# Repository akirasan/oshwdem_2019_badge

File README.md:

# oshwdem_2019_badge
Badge Oshwi para la OSHWDem 2019

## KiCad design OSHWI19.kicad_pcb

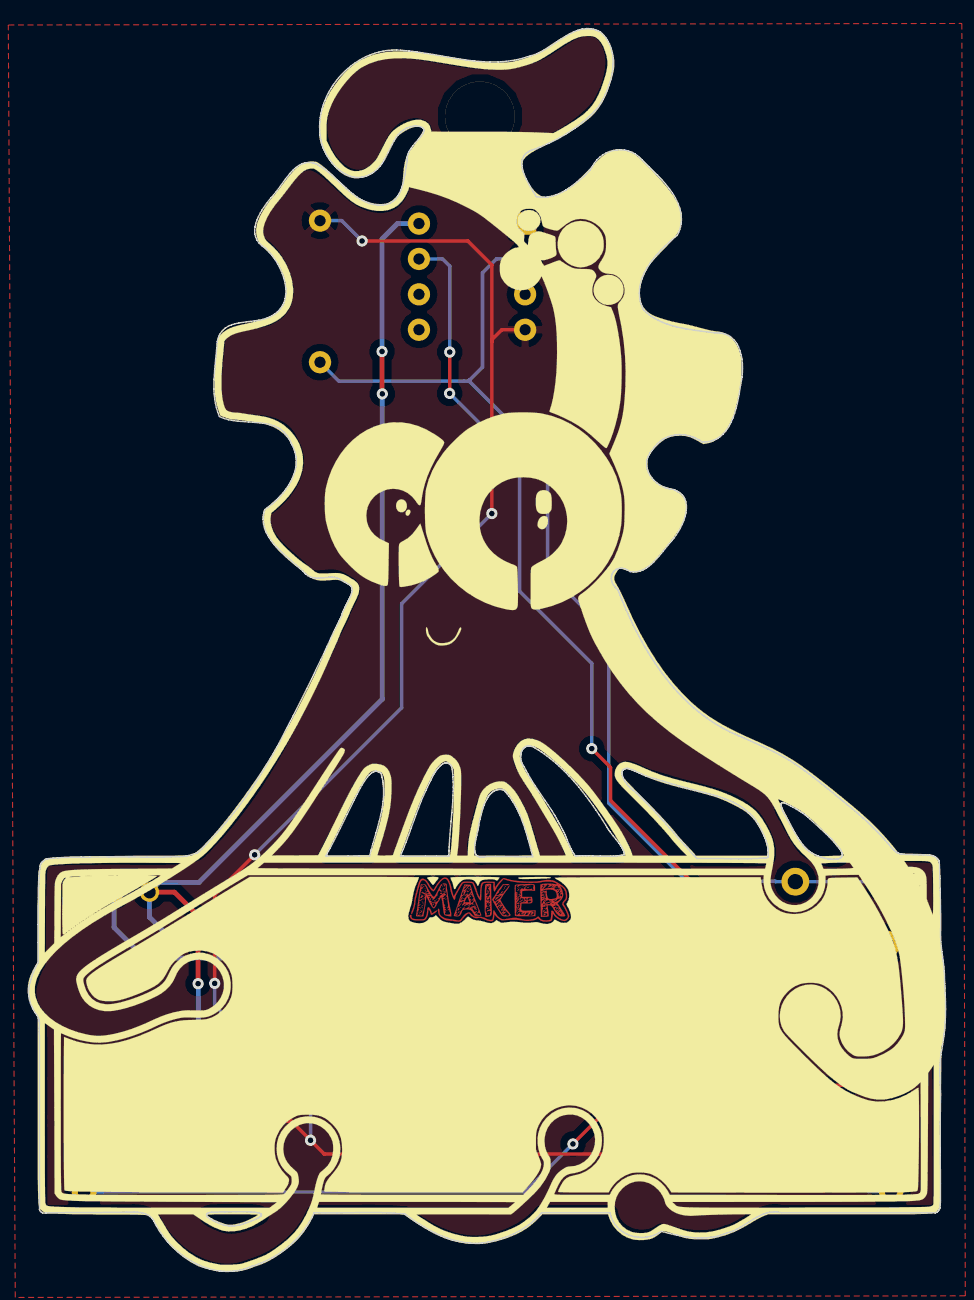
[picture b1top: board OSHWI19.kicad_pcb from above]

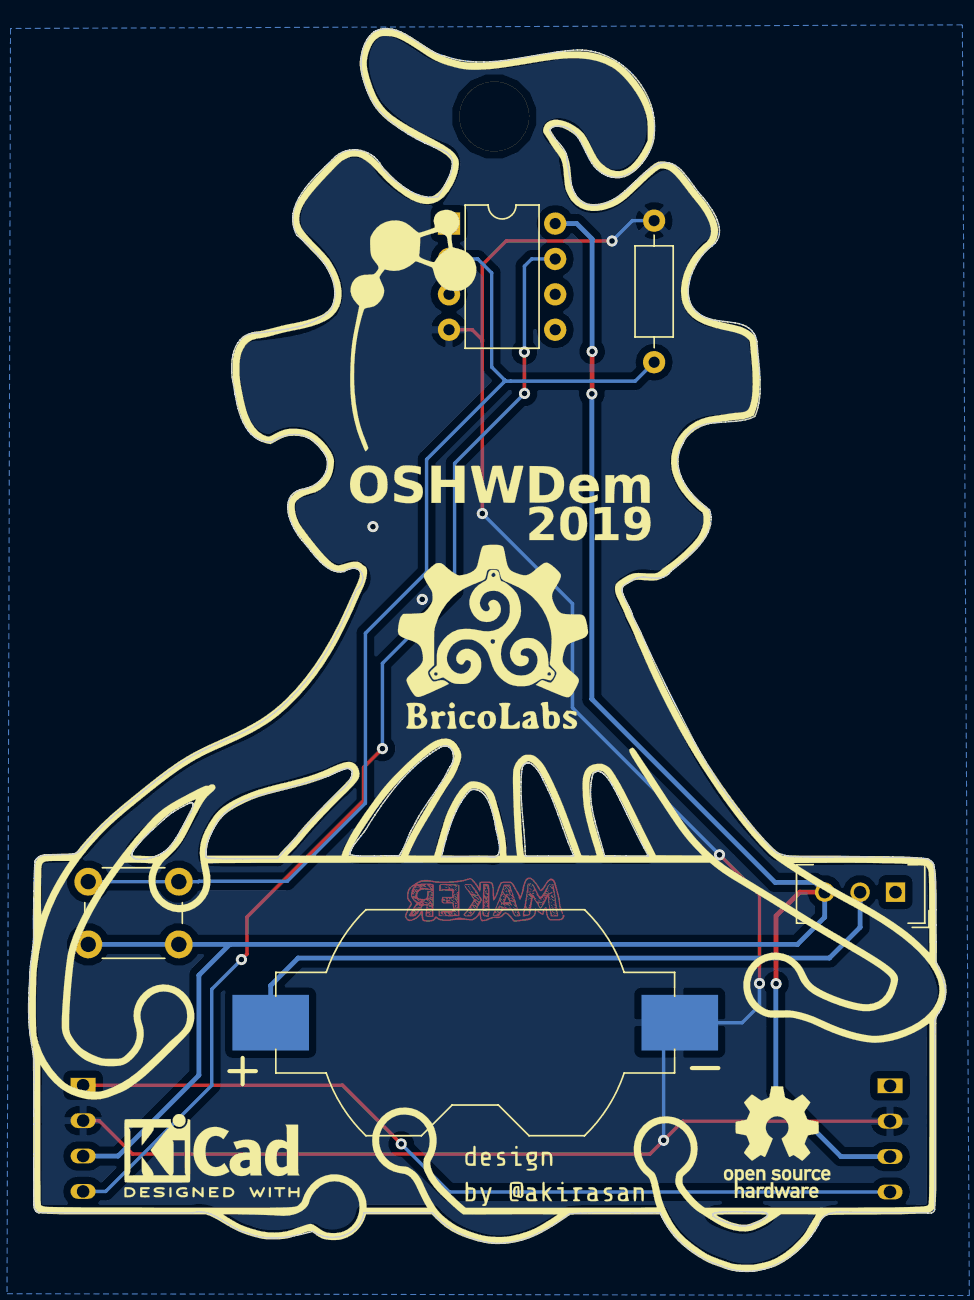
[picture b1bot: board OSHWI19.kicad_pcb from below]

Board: 2 copper layers, 65.8 x 89.2 mm, 8 parts (5 on the bottom side), 6 nets.

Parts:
BT1: Battery_Cell; BatteryHolder_Keystone_1058_1x2032
D1, D2: WS2812B; LED_D5.0mm-4
R1: R; R_Axial_DIN0207_L6.3mm_D2.5mm_P10.16mm_Horizontal
Ref**: Val**; OSHWI_pcb_v3
SW1: SW_Push; SW_PUSH_6mm_H4.3mm
SW2: SW_SPST; switch_slide
U1: ATTINY85-20PU; DIP-8_W7.62mm

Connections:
GND: BT1.2, D1.3, D2.3, R1.1, U1.4
unnamed: BT1.1, SW2.2
unnamed: D1.1, D2.1, SW1.1, SW2.3, U1.8
unnamed: D1.2, D2.4
unnamed: D1.4, U1.7
unnamed: R1.2, SW1.2, U1.2

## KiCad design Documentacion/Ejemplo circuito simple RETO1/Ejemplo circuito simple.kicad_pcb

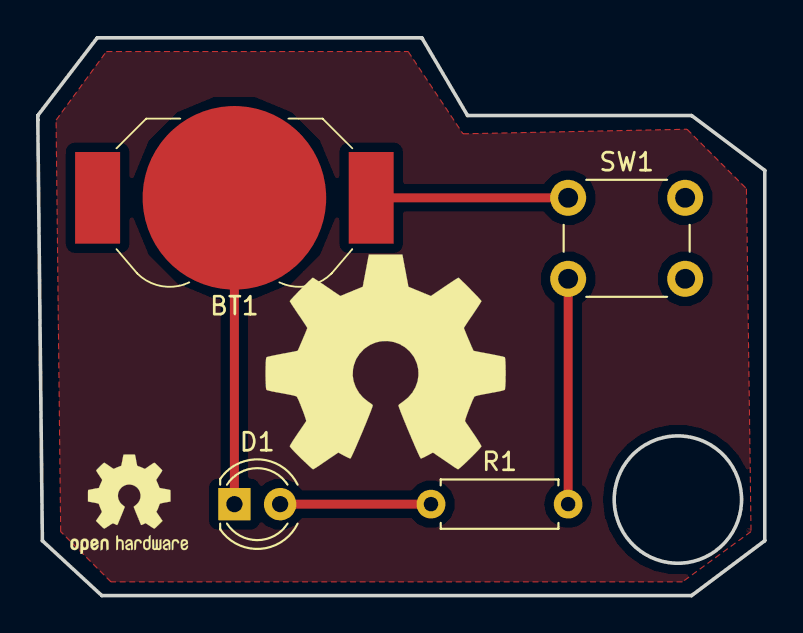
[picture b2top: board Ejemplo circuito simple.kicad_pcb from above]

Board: 2 copper layers, 40.4 x 31.0 mm, 4 parts (0 on the bottom side), 4 nets.

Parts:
BT1: Battery_Cell; BatteryHolder_LINX_BAT-HLD-012-SMT
D1: LED; LED_D4.0mm
R1: R; R_Axial_DIN0207_L6.3mm_D2.5mm_P7.62mm_Horizontal
SW1: SW_Push; SW_PUSH_6mm_H5mm

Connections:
unnamed: BT1.1, SW1.1
unnamed: BT1.2, D1.1
unnamed: D1.2, R1.1
unnamed: R1.2, SW1.2
